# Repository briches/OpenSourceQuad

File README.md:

<b>OpenSourceQuad</b>
==========

<b>Author</b>: Brandon Riches<br />

Started in May of 2013, and always a work in progress! <br />

Feel free to <b>[fork](https://github.com/briches/OpenSourceQuad/fork)</b> the repo and submit a pull request.  

Released under the GNU Public License  

<b>Programming the flight controller:</b>  
----

(Finally) <b>Safe Fuse Bytes</b>  
<code>lfuse = 0xD6, hfuse = 0xB1, efuse = 0xfd</code>  

<b>Using arduino avrisp:</b>  
<code>avrdude -P comport -b 19200 -c avrisp -p m2560 -v -e -U flash:w:hexfilename.hex</code>  
<b>Using USBasp</b>  
<code>avrdude -c usbasp -p m2560 -v -e -U flash:w:tmp.hex</code>  
<b>Writing fuse bits</b>  
<code>avrdude -c usbasp -p m2560 -U hfuse:w:0xB1:m -U lfuse:w:0xD6:m -U efuse:w:0xFD:m</code>

<b>ESC Settings</b>  
- Batt Type: LiXX
- Cut off: high
- Cut off Type: hard
- Brake: off
- Timing: auto
- Start up: medium

Description
-----------

Quadcopter flight firmware! 

The end goal is to create future proof, easy-to-use 
and customizable firmware for any flight configuration ( which is quite the lofty goal, but I'm working on it).
<br /><br />

<br />
Sensors:
 - LSM303 Accelerometer / Magnetometer 
 - MPU3050 Gyro
 - Adafruit ultimate GPS module
 - Maxbotix USRF (LV-EZ1)
 - BMP085 Barometeric Pressure/Temperature/Altitude

Features and long term goals:
----------------------------
   <br />
  - Fully autonomous takeoff and landing. Has the option to be controlled via radio comms. <br />

  - 9DOF sensor module (IMU) with GPS and localization  <br />
  
  - Open source =]
   <br />
   <br />

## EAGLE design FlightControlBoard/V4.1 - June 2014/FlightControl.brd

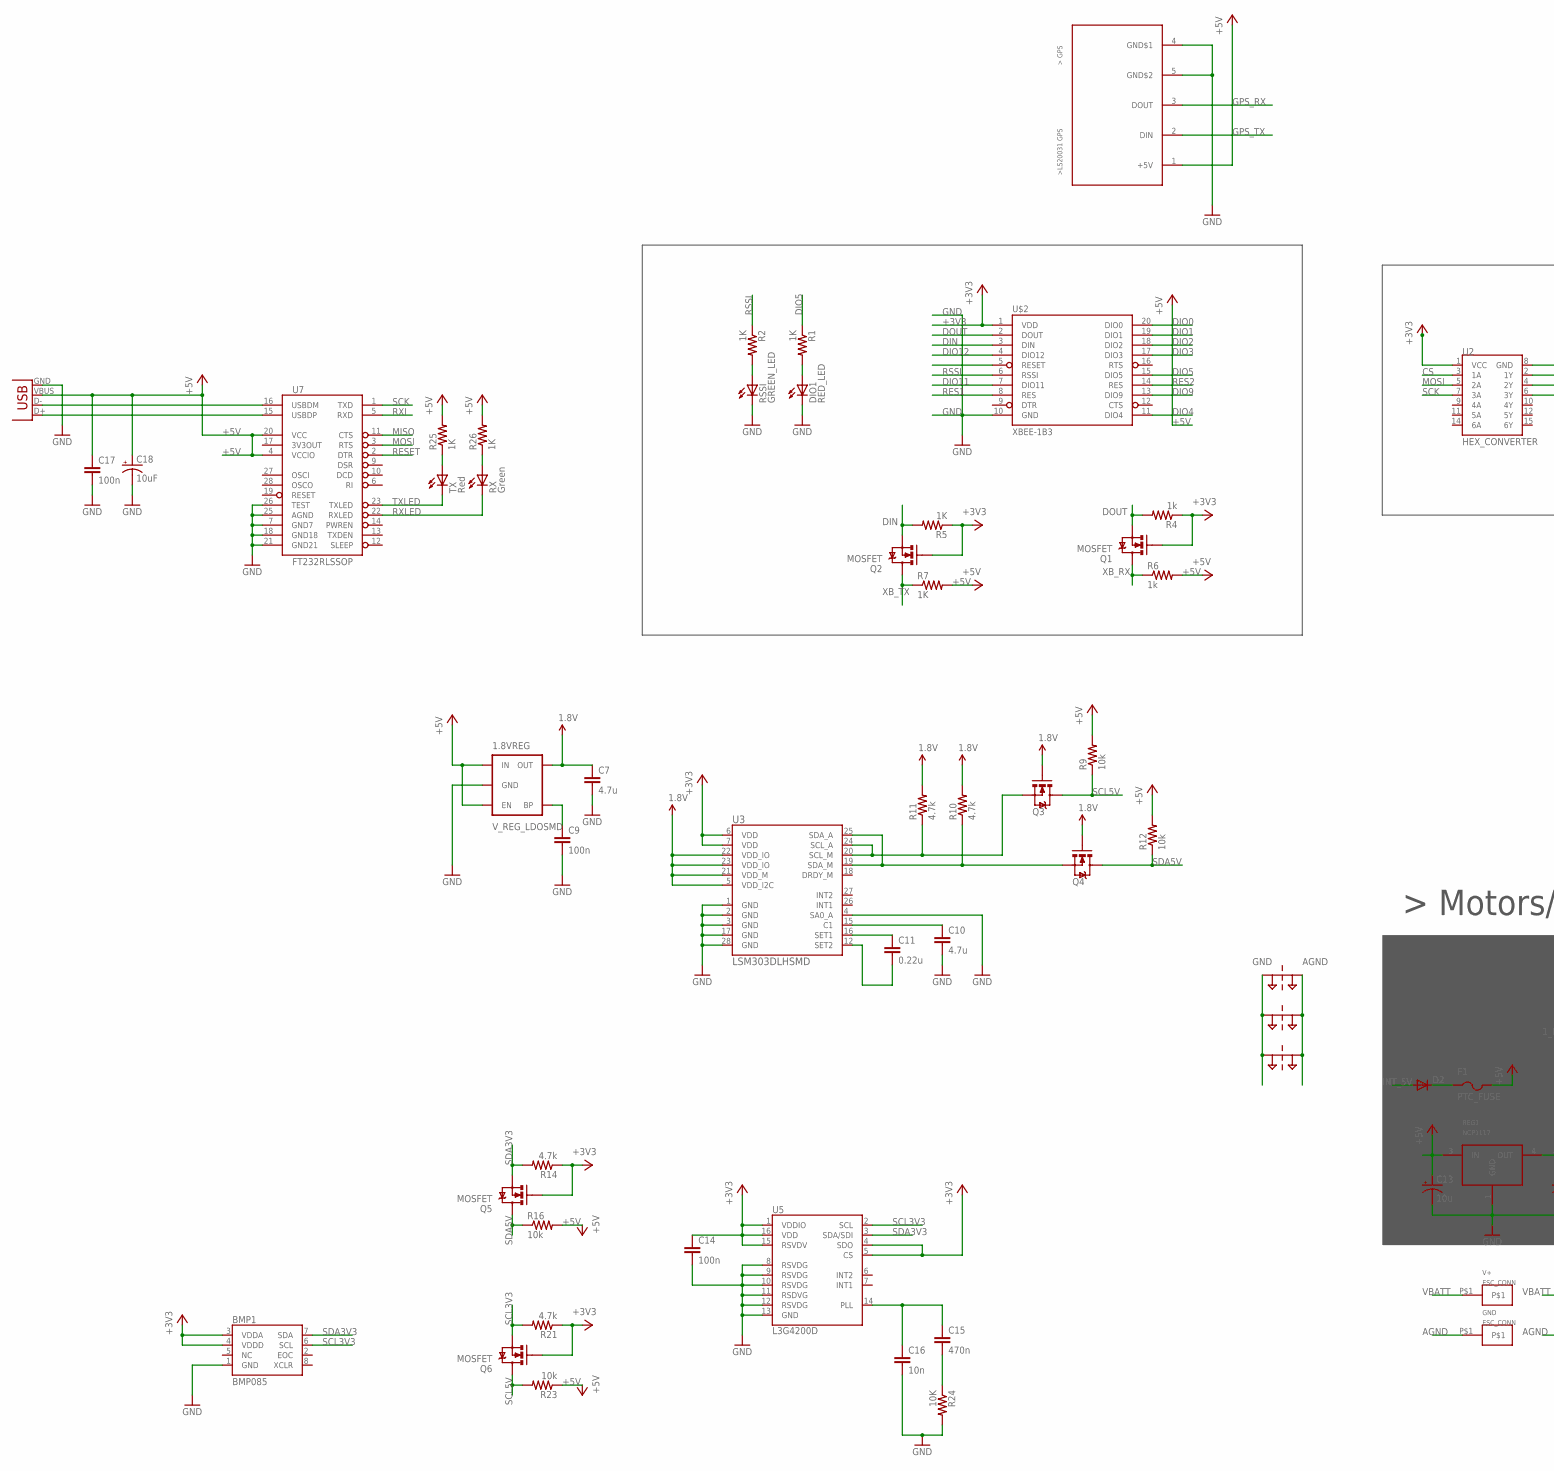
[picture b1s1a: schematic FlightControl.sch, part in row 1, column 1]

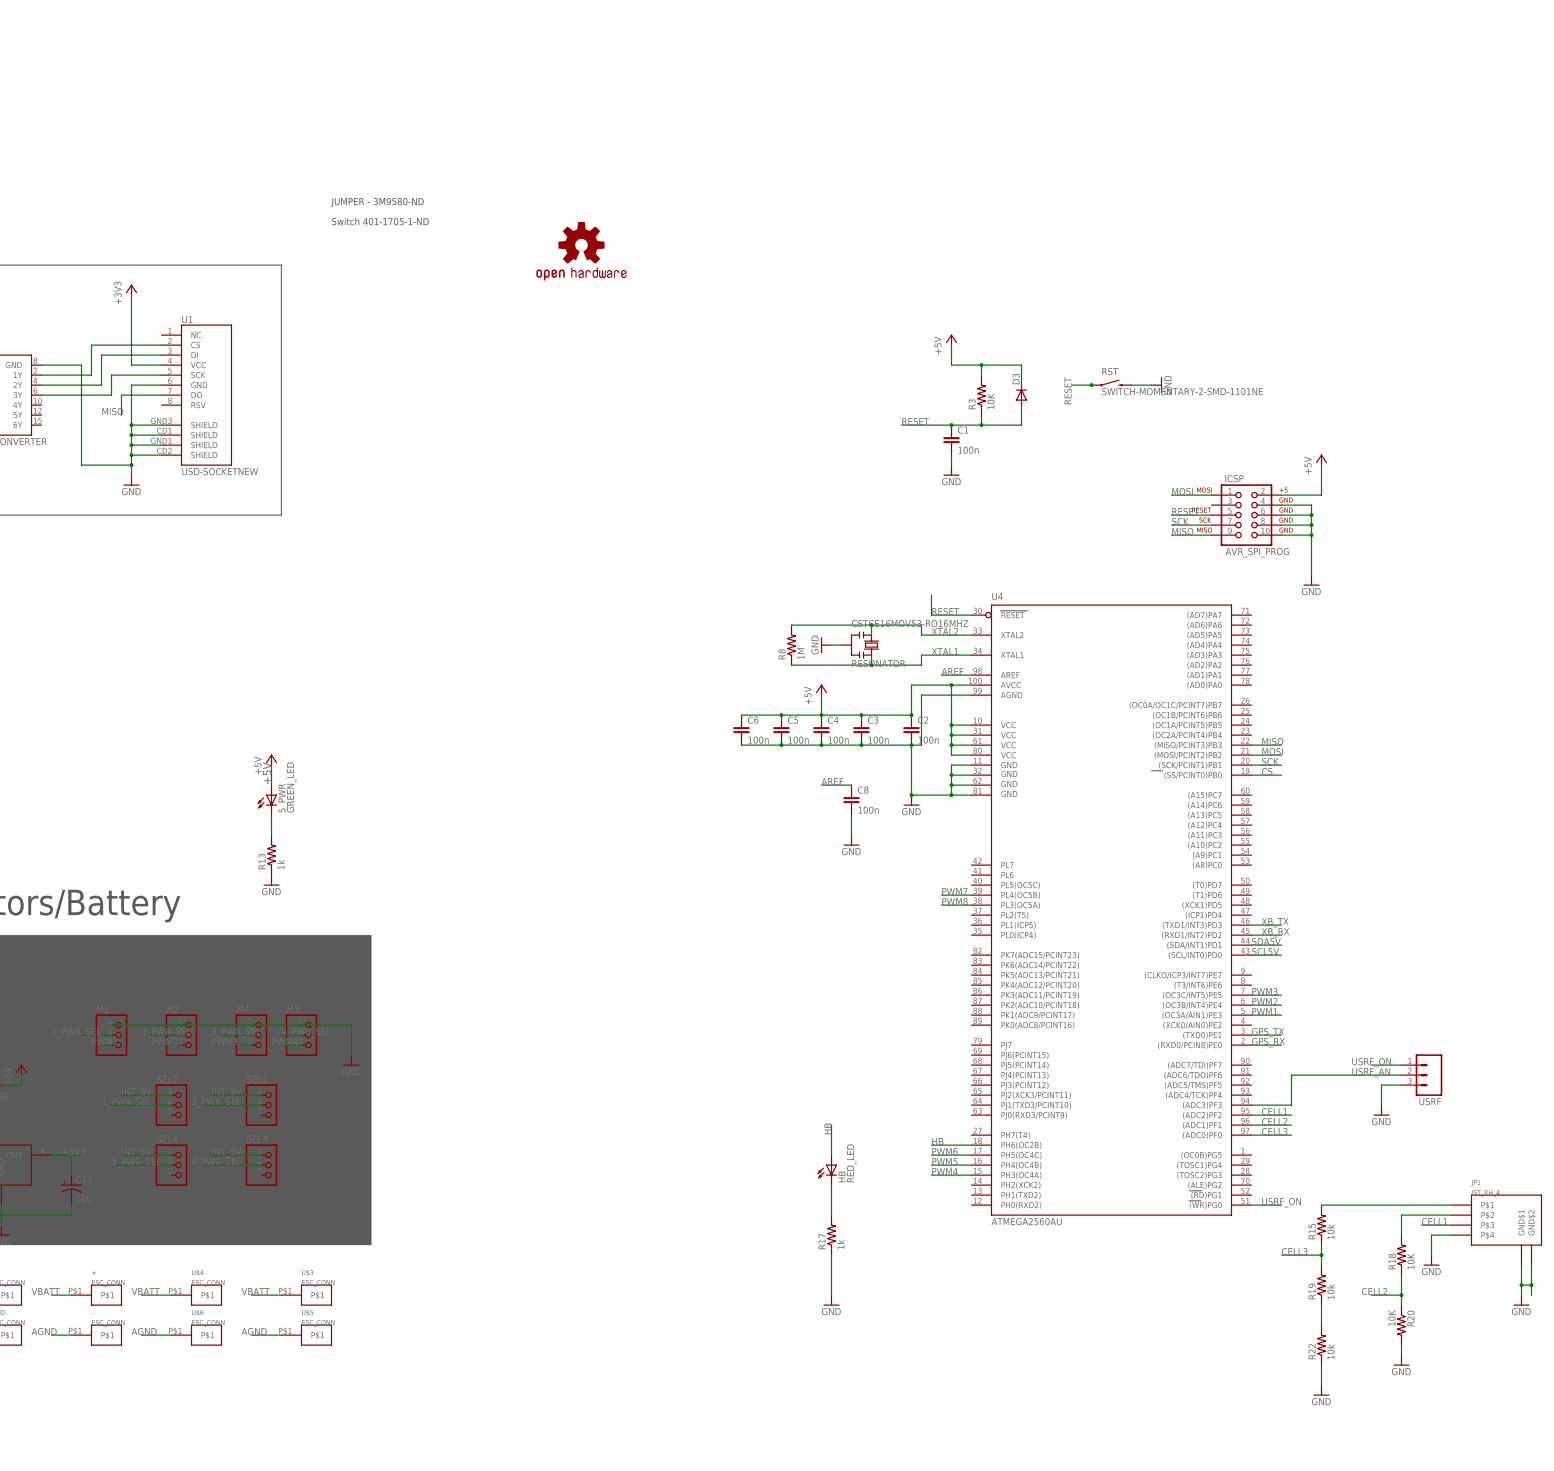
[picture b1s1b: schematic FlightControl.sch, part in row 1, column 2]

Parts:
1.8VREG: V_REG_LDOSMD; SOT23-5
5_PWR: GREEN_LED; LED-0603
+: ESC_CONN
-: ESC_CONN
BMP1: BMP085
C1, C2, C3, C4, C5, C6, C8, C9, C14, C17: 100n; 0402-CAP
C7, C10: 4.7u; 0402-CAP
C11: 0.22u; 0402-CAP
C12, C13: 10u; EIA3216
C15: 470n; 0402-CAP
C16: 10n; 0402-CAP
C18: 10uF; EIA3216
CSTCE16MOV53-RO16MHZ: RESONATOR
D2, D3: SCHOTTKY-1206D1206; C1206
DIO1: RED_LED; LED-0603
F1: PTC_FUSE; 1812
GND: ESC_CONN
HB: RED_LED; LED-0603
ICSP: AVR_SPI_PROG; AVR_ICSP
JP1: JST_XH_4; JST-XH4
LOGO1: OSHW-LOGOL; OSHW-LOGO-L
M1, M2, M3, M4: PINHD-1X3; 1X03
PT1, PT2, PT3: 2PT_GND_TIE
Q1, Q2, Q3, Q4, Q5, Q6: MOSFET; SOT23
R1, R2, R5, R7, R25, R26: 1K; 0603-RES
R3, R18, R20, R24: 10K; 0603-RES
R4, R6, R13, R17: 1k; 0603-RES
R8: 1M; 0603-RES
R9, R12, R15, R16, R19, R22, R23: 10k; 0603-RES
R10: 4.7k; 0402-RES
R11, R14, R21: 4.7k; 0603-RES
REG1: NCP1117; DPAK
RSSI: GREEN_LED; LED-0603
RST: SWITCH-MOMENTARY-2-SMD-1101NE; TACTILE-SWITCH-1101NE
RX: Green; LED-0603
SEL1, SEL2, SEL3, SEL4: PINHD-1X3; 1X03
TX: Red; LED-0603
U1: USD-SOCKETNEW; MICRO-SD-SOCKET-PP
U2: HEX_CONVERTER; SO016
U3: LSM303DLHSMD; LGA28-5X5
U4: ATMEGA2560AU; TQFP100
U5: L3G4200D; LGA16-4X4
U7: FT232RLSSOP; SSOP28DB
U$1: LS20031
U$2: XBEE-1B3; XBEE-SMD
U$3, U$4, U$5, U$6: ESC_CONN
USRF: M03LOCK; 1X03_LOCK
V+: ESC_CONN
X2: USB-SMD-NS; USB-MINIB-NOSTOP

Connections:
1.8V: 1.8VREG.5 (OUT), C7.1, Q3.1 (G), Q4.1 (G), R10.2, R11.2, U3.5 (VDD_I2C), U3.21 (VDD_M), U3.22 (VDD_IO), U3.23 (VDD_IO)
1_PWR_SEL: M1.2, SEL2.2
2_PWR_SEL: M2.2, SEL1.2
3_PWR_SEL: M4.2, SEL4.2
4_PWR_SEL: M3.2, SEL3.2
+3V3: BMP1.3 (VDDA), BMP1.4 (VDDD), C12.A (+), C14.1, Q1.1 (G), Q2.1 (G), Q5.1 (G), Q6.1 (G), R4.1, R5.1, R14.1, R21.1, REG1.4 (OUT), U1.4 (VCC), U2.1 (VCC), U3.6 (VDD), U3.7 (VDD), U5.1 (VDDIO), U5.4 (SDO), U5.5 (CS), U5.15 (RSVDV), U5.16 (VDD), U$2.1 (VDD)
+5V: 1.8VREG.1 (IN), 1.8VREG.3 (EN), 5_PWR.A, C2.1, C3.1, C4.1, C5.1, C6.1, C13.A (+), C17.1, C18.A (+), D3.2 (C), F1.2, ICSP.2, R3.2, R6.2, R7.2, R9.2, R12.2, R16.2, R23.1, R25.2, R26.2, REG1.3 (IN), U4.10 (VCC), U4.31 (VCC1), U4.61 (VCC2), U4.80 (VCC3), U4.100 (AVCC), U7.4 (VCCIO), U7.20 (VCC), U$1.1 (+5V), X2.VBUS
AGND: -.P$1, GND.P$1, PT1.P$2, PT2.P$2, PT3.P$2, U$5.P$1, U$6.P$1
AREF: C8.1, U4.98 (AREF)
CELL1: JP1.P$3, U4.95 ((ADC2)PF2)
CELL2: R18.1, R20.1, U4.96 ((ADC1)PF1)
CELL3: R15.1, R19.2, U4.97 ((ADC0)PF0)
CS: U2.3 (1A), U4.19 ((SS/PCINT0)PB0)
DIN: Q2.2 (S), R5.2, U$2.3 (DIN)
DIO0: U$2.20 (DIO0)
DIO1: U$2.19 (DIO1)
DIO2: U$2.18 (DIO2)
DIO3: U$2.17 (DIO3)
DIO4: U$2.11 (DIO4)
DIO5: R1.1, U$2.15 (DIO5)
DIO9: U$2.13 (DIO9)
DIO11: U$2.7 (DIO11)
DIO12: U$2.4 (DIO12)
DOUT: Q1.2 (S), R4.2, U$2.2 (DOUT)
GND: 1.8VREG.2 (GND), BMP1.1 (GND), C1.2, C2.2, C3.2, C4.2, C5.2, C6.2, C7.2, C8.2, C9.2, C10.2, C12.C (-), C13.C (-), C14.2, C16.2, C17.2, C18.C (-), CSTCE16MOV53-RO16MHZ.2, DIO1.C, ICSP.4, ICSP.6, ICSP.8, ICSP.10, JP1.GND$1, JP1.GND$2, JP1.P$4, M1.1, M2.1, M3.1, M4.1, PT1.P$1, PT2.P$1, PT3.P$1, R13.1, R17.1, R20.2, R22.1, R24.2, REG1.1 (GND), RSSI.C, RST.P$2 (2), U1.6 (GND), U1.CD1 (SHIELD), U1.CD2 (SHIELD), U1.GND1 (SHIELD), U1.GND3 (SHIELD), U2.8 (GND), U3.1 (GND), U3.2 (GND), U3.3 (GND), U3.4 (SA0_A), U3.17 (GND), U3.28 (GND), U4.11 (GND), U4.32 (GND1), U4.62 (GND2), U4.81 (GND3), U4.99 (AGND), U5.8 (RSVDG), U5.9 (RSVDG), U5.10 (RSVDG), U5.11 (RSDVG), U5.12 (RSVDG), U5.13 (GND), U7.7 (GND7), U7.18 (GND18), U7.21 (GND21), U7.25 (AGND), U7.26 (TEST), U$1.4 (GND$1), U$1.5 (GND$2), U$2.10 (GND), USRF.3, X2.GND
GPS_RX: U4.2 ((RXD0/PCIN8)PE0), U$1.3 (DOUT)
GPS_TX: U4.3 ((TXD0)PE1), U$1.2 (DIN)
HB: HB.A, U4.18 (PH6(OC2B))
INT_5V: D2.1 (A), SEL1.1, SEL2.1, SEL3.1, SEL4.1
MISO: ICSP.9, U1.7 (DO), U4.22 ((MISO/PCINT3)PB3), U7.11 (CTS)
MOSI: ICSP.1, U2.5 (2A), U4.21 ((MOSI/PCINT2)PB2), U7.3 (RTS)
unnamed: R19.1, R22.2
unnamed: 1.8VREG.4 (BP), C9.1
unnamed: U1.2 (CS), U2.2 (1Y)
unnamed: U1.3 (DI), U2.4 (2Y)
unnamed: U1.5 (SCK), U2.6 (3Y)
unnamed: C11.1, U3.16 (SET1)
unnamed: 5_PWR.C, R13.2
unnamed: DIO1.A, R1.2
unnamed: R2.2, RSSI.A
unnamed: HB.C, R17.2
unnamed: R25.1, TX.A
unnamed: C11.2, U3.12 (SET2)
unnamed: C10.1, U3.15 (C1)
unnamed: D2.2 (C), F1.1
unnamed: Q3.2 (S), R11.1, U3.20 (SCL_M), U3.24 (SCL_A)
unnamed: Q4.2 (S), R10.1, U3.19 (SDA_M), U3.25 (SDA_A)
unnamed: JP1.P$2, R18.2
unnamed: C15.1, C16.1, U5.14 (PLL)
unnamed: C15.2, R24.1
unnamed: JP1.P$1, R15.2
unnamed: R26.1, RX.A
PWM1: M1.3, U4.5 ((OC3A/AIN1)PE3)
PWM2: M2.3, U4.6 ((OC3B/INT4)PE4)
PWM3: M4.3, U4.7 ((OC3C/INT5)PE5)
PWM4: M3.3, U4.15 (PH3(OC4A))
PWM5: U4.16 (PH4(OC4B))
PWM6: U4.17 (PH5(OC4C))
PWM7: U4.39 (PL4(OC5B))
PWM8: U4.38 (PL3(OC5A))
RES1: U$2.8 (RES)
RES2: U$2.14 (RES)
RESET: C1.1, D3.1 (A), ICSP.5, R3.1, RST.P$1 (1), U4.30 (RESET), U7.2 (DTR)
RSSI: R2.1, U$2.6 (RSSI)
RXI: U7.5 (RXD)
RXLED: RX.C, U7.22 (RXLED)
SCK: ICSP.7, U2.7 (3A), U4.20 ((SCK/PCINT1)PB1), U7.1 (TXD)
SCL3V3: BMP1.6 (SCL), Q6.2 (S), R21.2, U5.2 (SCL)
SCL5V: Q3.3 (D), Q6.3 (D), R9.1, R23.2, U4.43 ((SCL/INT0)PD0)
SDA3V3: BMP1.7 (SDA), Q5.2 (S), R14.2, U5.3 (SDA/SDI)
SDA5V: Q4.3 (D), Q5.3 (D), R12.1, R16.1, U4.44 ((SDA/INT1)PD1)
TXLED: TX.C, U7.23 (TXLED)
USB_D+: U7.15 (USBDP), X2.D+
USB_D-: U7.16 (USBDM), X2.D-
USRF_AN: U4.94 ((ADC3)PF3), USRF.2
USRF_ON: U4.51 ((WR)PG0), USRF.1
VBATT: +.P$1, U$3.P$1, U$4.P$1, V+.P$1
XB_RX: Q1.3 (D), R6.1, U4.45 ((RXD1/INT2)PD2)
XB_TX: Q2.3 (D), R7.1, U4.46 ((TXD1/INT3)PD3)
XTAL1: CSTCE16MOV53-RO16MHZ.3, R8.1, U4.34 (XTAL1)
XTAL2: CSTCE16MOV53-RO16MHZ.1, R8.2, U4.33 (XTAL2)

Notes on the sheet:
JUMPER - 3M9580-ND
Switch 401-1705-1-ND

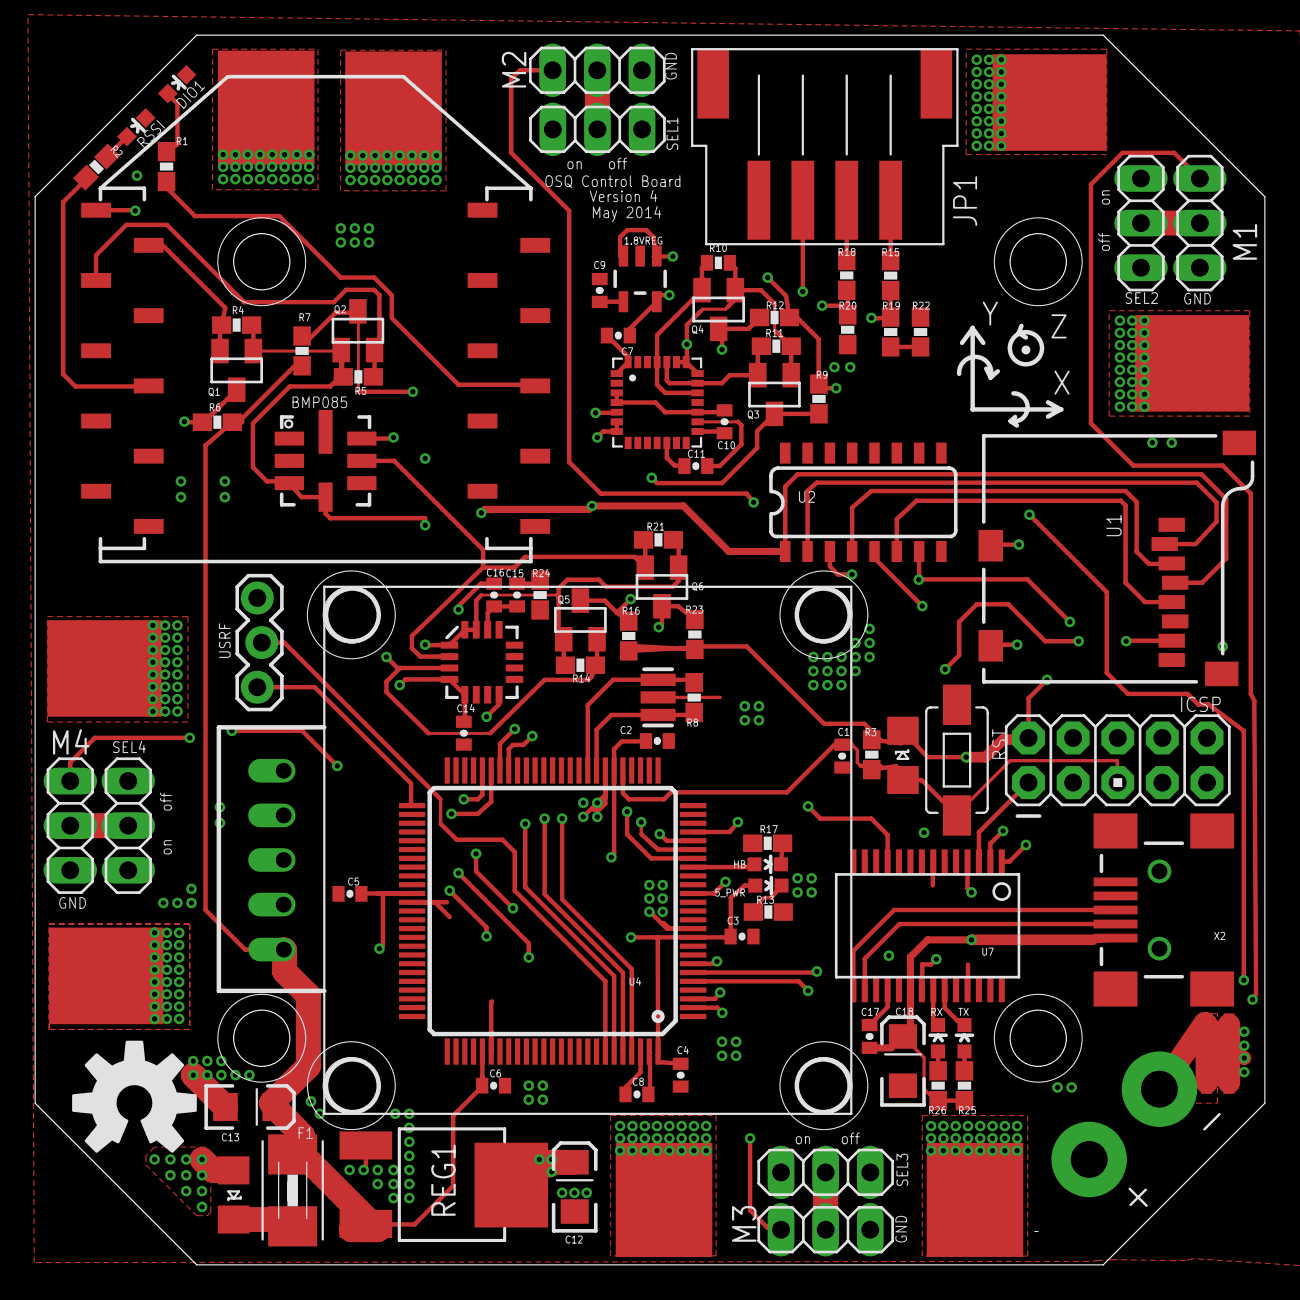
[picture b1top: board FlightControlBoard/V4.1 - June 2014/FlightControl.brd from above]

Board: 4 copper layers, 70.0 x 70.0 mm, 96 parts (0 on the bottom side), 66 nets.

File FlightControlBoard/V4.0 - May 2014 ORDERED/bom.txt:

Qty,Value,Device,Package,Parts,,,,Description,PROD_ID
4,LED,LED0603,LED-0603,"5_PWR, DIO1, HB, RSSI",,,,LEDs,
1,,M03LOCK,1X03_LOCK,USRF,,,,Header 3,
8,,PINHD-1X3,1X03,"M1, M2, M3, M4, SEL1, SEL2, SEL3, SEL4",,,,PIN HEADER,
1,500ma,PTCFUSE-1812,1812,F1,,,,"PTC fuses, resettable thermi",stors
1,0.22u,CAP0402-CAP,0402-CAP,C11,,,,Capacitor,
8,100n,CAP0402-CAP,0402-CAP,"C1, C2, C3, C4, C5, C","6,","C8,",C14,Capacitor,
4,10K,RESISTOR0402-RES,0402-RES,"R3, R18, R20, R24",,,,Resistor,
7,10k,RESISTOR0402-RES,0402-RES,"R9, R12, R15, R16, R1","9,",R22,", R23",Resistor,
1,10n,CAP0402-CAP,0402-CAP,C16,,,,Capacitor,
4,1K,RESISTOR0402-RES,0402-RES,"R1, R2, R5, R7",,,,Resistor,
1,1M,RESISTOR0402-RES,0402-RES,R8,,,,Resistor,
4,1k,RESISTOR0402-RES,0402-RES,"R4, R6, R13, R17",,,,Resistor,
4,4.7k,RESISTOR0402-RES,0402-RES,"R10, R11, R14, R21",,,,Resistor,
2,4.7u,C-EUC3216,C3216,"C12, C13",,,,"CAPACITOR, European symbol",
3,4.7u,CAP0402-CAP,0402-CAP,"C7, C9, C10",,,,Capacitor,
1,470n,CAP0402-CAP,0402-CAP,C15,,,,Capacitor,
1,ATMEGA2560AU,ATMEGA2560AU,TQFP100,U4,,,,Atmel 100-pin 8-bit uC,
1,AVR_SPI_PROG,AVR_SPI_PROG,AVR_ICSP,ICSP,,,,AVR 10-pin ICSP Header,
1,BMP085,BMP085,BMP085,BMP1,,,,BMP085 Pressure Sensor Great,little MEMS pressure sensor. SKU: COM-09603
8,ESC_CONN,ESC_CONN,ESC_CONN,"+, -, GND, U$3, U$4,",U$,"5, U","$6, V+",,
1,HEX_CONVERTER,HEX_CONVERTER,SO016,U2,,,,Just what it says.,
1,JST_XH_4,JST_XH_4,JST-XH4,JP1,,,,,
1,L3G4200D,L3G4200D,LGA16-4X4,U5,,,,"L3G4200D Three-axis, digital",output gyroscope
1,LS20031,LS20031,LS20031,U$1,,,,,
1,LSM303DLHSMD,LSM303DLHSMD,LGA28-5X5,U3,,,,I2C accelerometer/magnetomet,er/tilt compensated compass
6,MOSFET,MOSFET-NCHANNELBSS138,SOT23,"Q1, Q2, Q3, Q4, Q5, Q",6,,,Common NMOSFET Parts,TRANS-00830
1,NCP1117,NCP1117,DPAK,REG1,,,,,
1,RESONATOR,RESONATORMU,RESONATOR,CSTCE16MOV53-RO16MHZ,,,,,
2,SCHOTTKY-1206,D1206            SCHOTTKY-1206D1206,C1206,"D2, D3",,,,,
1,SWITCH-MOMENT,ARY-2-SMD-1101NE SWITCH-MOMENTARY-2-SMD-1101NE,TACTILE-SWITCH-1101NE,RST,,,,Various NO switches- pushbut,"tons, reed, etc"
1,USD-SOCKETNEW,USD-SOCKETNEW,MICRO-SD-SOCKET-PP,U1,,,,microSD Socket,
1,V_REG_LDOSMD,V_REG_LDOSMD,SOT23-5,1.8VREG,,,,Voltage Regulator LDO,
1,XBEE-1B3,XBEE-1B3,XBEE-SMD,U$2,,,,Xbee module footprints,CONN-09042
,,,,,,,,,
,,,,,,,,,
,Qty,Part Number,Manufacturer,Package,Reference,Description,Digi-Key P/N,Mouser P/N,Newark P/N
Capacitors,,,,,,,,,

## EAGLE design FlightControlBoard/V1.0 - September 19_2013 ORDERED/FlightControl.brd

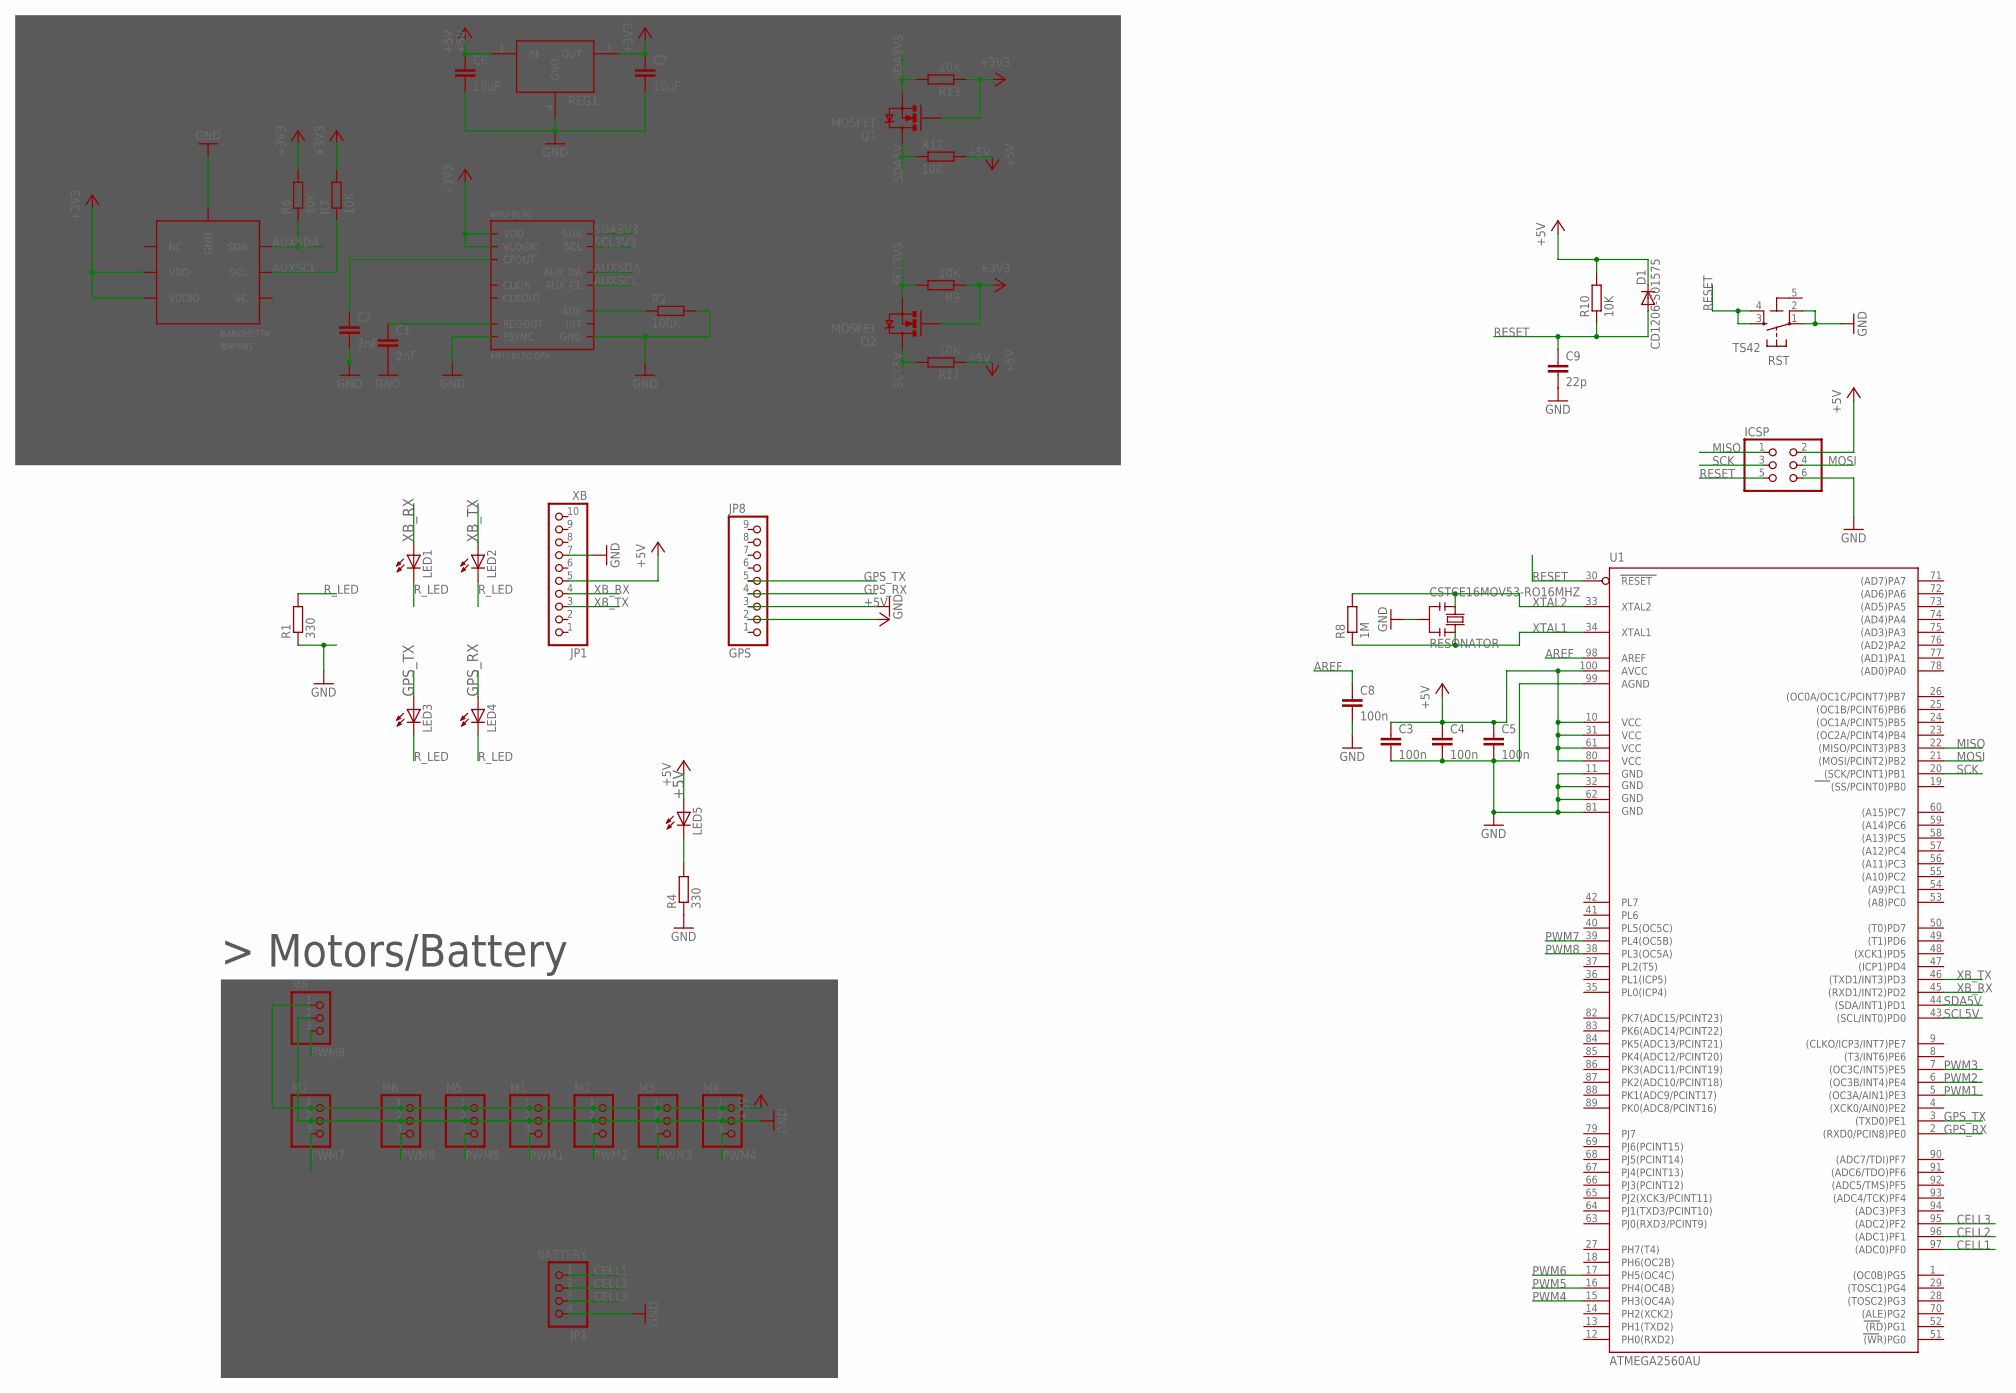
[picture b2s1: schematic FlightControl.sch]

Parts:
BAROMETRIC: BMP085; 7LGA
BATTERY: JP1; 1X04
C1, C2: 2nF; C0603-ROUND
C3, C4, C5, C8: 100n; C0603-ROUND
C6, C7: 10uF; CAP-PTH-SMALLEZ
C9: 22p; C0603-ROUND
CSTCE16MOV53-RO16MHZ: RESONATOR
D1: CD1206-S01575; MINIMELF
GPS: JP8; 1X09
ICSP: PINHD-2X3; 2X03
JP1: XB; 1X10
LED1, LED2, LED3, LED4, LED5: LEDCHIPLED_1206; CHIPLED_1206
M1, M2, M3, M4, M5, M6, M7, M8: PINHD-1X3; 1X03
MPU-9150: MPU-9150.QFN; QFN.24.4X4
Q1, Q2: MOSFET; SOT23
R1, R4: 330; R0603-ROUND
R2: 100K; R0603-ROUND
R6, R7, R9, R10, R11, R12, R13: 10K; R0603-ROUND
R8: 1M; R0603-ROUND
REG1: LD39300; DPAK
RST: TS42
U1: ATMEGA2560AU; TQFP100

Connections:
5-GND: RST.5 (5-GND)
+3V3: BAROMETRIC.2 (VDD), BAROMETRIC.3 (VDDIO), C7.1, MPU-9150.3 (VDD), MPU-9150.8 (VLOGIC), MPU-9150.13 (VDD), Q1.1 (G), Q2.1 (G), R6.2, R7.2, R9.1, R13.1, REG1.3 (OUT)
+5V: C3.1, C4.1, C5.1, C6.1, D1.C, GPS.2, ICSP.2, JP1.5, LED5.A, M1.1, M2.1, M3.1, M4.1, M5.1, M6.1, M7.1, M8.1, R10.2, R11.1, R12.2, REG1.1 (IN), U1.10 (VCC), U1.31 (VCC1), U1.61 (VCC2), U1.80 (VCC3), U1.100 (AVCC)
AD0: MPU-9150.9 (AD0), R2.1
AREF: C8.1, U1.98 (AREF)
AUXSCL: BAROMETRIC.5 (SCL), MPU-9150.7 (AUX_CL), R7.1
AUXSDA: BAROMETRIC.6 (SDA), MPU-9150.6 (AUX_DA), R6.1
CELL1: BATTERY.1, U1.97 ((ADC0)PF0)
CELL2: BATTERY.2, U1.96 ((ADC1)PF1)
CELL3: BATTERY.3, U1.95 ((ADC2)PF2)
CPOUT: C2.1, MPU-9150.20 (CPOUT)
GND: BAROMETRIC.7 (GND), BATTERY.4, C1.2, C2.2, C3.2, C4.2, C5.2, C6.2, C7.2, C8.2, C9.2, CSTCE16MOV53-RO16MHZ.2, GPS.3, ICSP.6, JP1.7, M1.2, M2.2, M3.2, M4.2, M5.2, M6.2, M7.2, M8.2, MPU-9150.11 (FSYNC), MPU-9150.15 (GND), MPU-9150.17 (GND), MPU-9150.18 (GND), R1.1, R2.2, R4.1, REG1.4 (GND), RST.1, RST.2, U1.11 (GND), U1.32 (GND1), U1.62 (GND2), U1.81 (GND3), U1.99 (AGND)
GPS_RX: GPS.4, LED4.A, U1.2 ((RXD0/PCIN8)PE0)
GPS_TX: GPS.5, LED3.A, U1.3 ((TXD0)PE1)
MISO: ICSP.1, U1.22 ((MISO/PCINT3)PB3)
MOSI: ICSP.4, U1.21 ((MOSI/PCINT2)PB2)
unnamed: LED5.C, R4.2
PWM1: M1.3, U1.5 ((OC3A/AIN1)PE3)
PWM2: M2.3, U1.6 ((OC3B/INT4)PE4)
PWM3: M3.3, U1.7 ((OC3C/INT5)PE5)
PWM4: M4.3, U1.15 (PH3(OC4A))
PWM5: M5.3, U1.16 (PH4(OC4B))
PWM6: M6.3, U1.17 (PH5(OC4C))
PWM7: M7.3, U1.39 (PL4(OC5B))
PWM8: M8.3, U1.38 (PL3(OC5A))
REGOUT: C1.1, MPU-9150.10 (REGOUT)
RESET: C9.1, D1.A, ICSP.5, R10.1, RST.3, RST.4, U1.30 (RESET)
R_LED: LED1.C, LED2.C, LED3.C, LED4.C, R1.2
SCK: ICSP.3, U1.20 ((SCK/PCINT1)PB1)
SCL3V3: MPU-9150.23 (SCL), Q2.2 (S), R9.2
SCL5V: Q2.3 (D), R11.2, U1.43 ((SCL/INT0)PD0)
SDA3V3: MPU-9150.24 (SDA), Q1.2 (S), R13.2
SDA5V: Q1.3 (D), R12.1, U1.44 ((SDA/INT1)PD1)
XB_RX: JP1.4, LED1.A, U1.45 ((RXD1/INT2)PD2)
XB_TX: JP1.3, LED2.A, U1.46 ((TXD1/INT3)PD3)
XTAL1: CSTCE16MOV53-RO16MHZ.3, R8.1, U1.34 (XTAL1)
XTAL2: CSTCE16MOV53-RO16MHZ.1, R8.2, U1.33 (XTAL2)

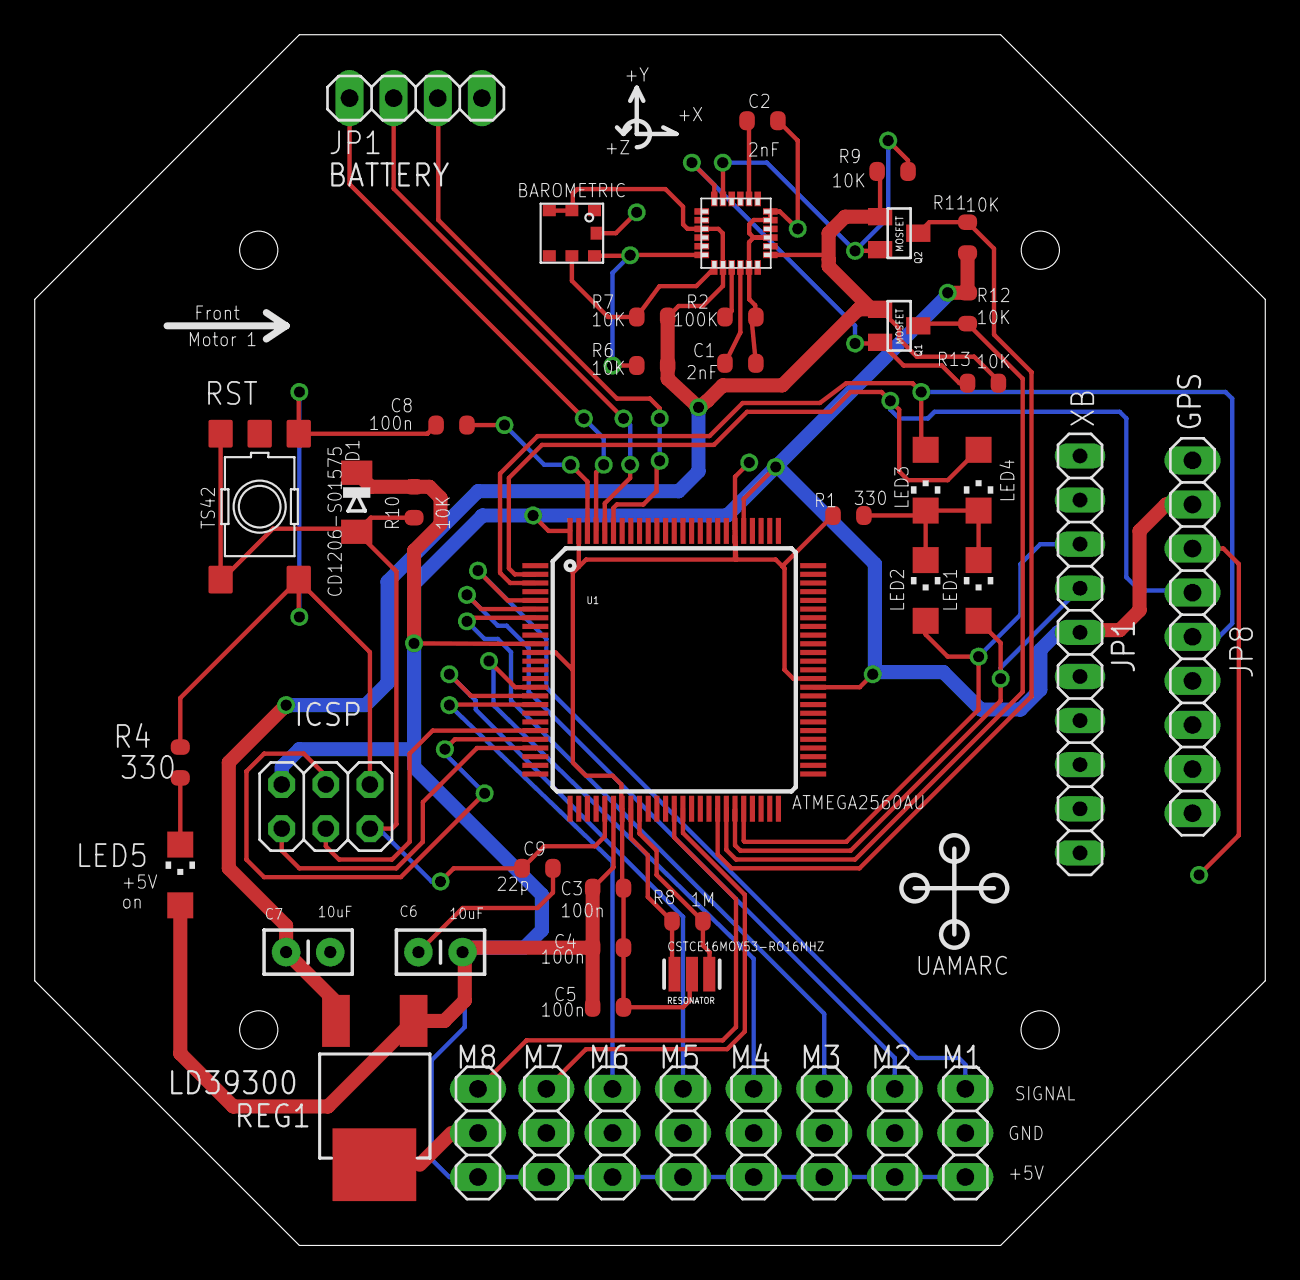
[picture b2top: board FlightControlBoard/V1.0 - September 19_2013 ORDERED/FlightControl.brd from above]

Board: 2 copper layers, 70.9 x 69.7 mm, 46 parts (0 on the bottom side), 36 nets.

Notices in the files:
parts and their libraries:
SparkFun-Capacitors: Licensing: CC v3.0 Share-Alike You are welcome to use this library for commercial purposes.
